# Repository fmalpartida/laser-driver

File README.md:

# Laser Driver
Small compact, constant current source for driving LEDs and lasers up to 4A with PWM capabilities and integrated support to drive 3 loads such as fans.

## Board specification
### Schematic
[Last version of the schematic](./documentation/laserDriver_schematic.pdf)

### Electrical characteristics
   **V(in) range:**  4V..18V, *observe input caps ratings*

   **Max. main load current:** 3.3A *observe inductor ratings*

   **Max. aux load currents:** 500mA *depends on transistor selection*

   **Dim. threshold voltage:** 1.2V

   **Duty cycle range:** 0%..100%

   **Soft start duration:** 1.2ms

   **Dim. frequency range:** 400Hz..4KHz

### Mechanical
   **Board dimensions:** 32mm x 32mm

   **Supply and main load dimming:** 1 x 3 pin, 2.54mm connector

   **Main load connector:** 1 x 2 pin, 2.54mm connector

   **Aux. load dimm. connector:** 1 x 3 pin, 2.54mm connector

   **Aux. load connector:** 3 x 2 pin, 2.54mm connector

   **PCB fabrication:** Pattern class 6, drills clase C. Any cheap PCB manufacturer should be more than capable of making your boards. *Do not shrink track widths.*

*Observe connector current ratings for your application.*

### Measured performance
   **Performance:** Measure performance 83% @ 12V, 1A load. Tested with a 3W LED.

## Operation and setup

Connect power supply to the supply and main load dimming connector observing the polarity
(V+, DIM, V-) within the board's tolerance and ensure that your supply is capable of sourcing
the current required by your load.

Connect the load (LED or laser driver) observing the polarity of your device.

If you use auxiliary loads connect them to the auxiliary load connectors and observe their polarity.
The board has built in freewheel diodes, you should be good to go with any type of load provided you don't
exceed switching ratings.

Each auxiliary load channel is controlled with a control signal from the aux load connector. By default
loads are inactive. A voltage level of 5V (depending on your FET selection) will activate each channel.

### Soft start
The board is configured to do a soft start. Apply a 1.2ms (minimum) pulse to the dimm pin before
starting the PWM operation.

## Waveforms and captures
A couple of waveform capture showing the performance of the driver. Measurement setup:
* Supply voltage: 5V
* Load current: 1A

To start the driver it needs a 1.1ms pulse on the dimming pin.

976Hz PWM duty cycle captures.

Raising edge, measuring directly the LED voltage on switch on. 10us, raising edge with very little
overshoot and ringing. Very decent current control and regulation.

Ripple and noise is around 20mV, I think that about half of it comes from my measurement setup. 20MHz
bandwidth limit.

## Disclaimer
The board has only been tested to switch a 3W LED driven at 1A. It should be more than capable of reaching
it's full specifications provided that you don't exceed the current ratings of the components you mount.

## License
The board is released under the CERN OHL v1.2 but if you like it and use it you can buy me some beer.
If you use it and/or do any derivative work from it, be nice and give attribution to the source.

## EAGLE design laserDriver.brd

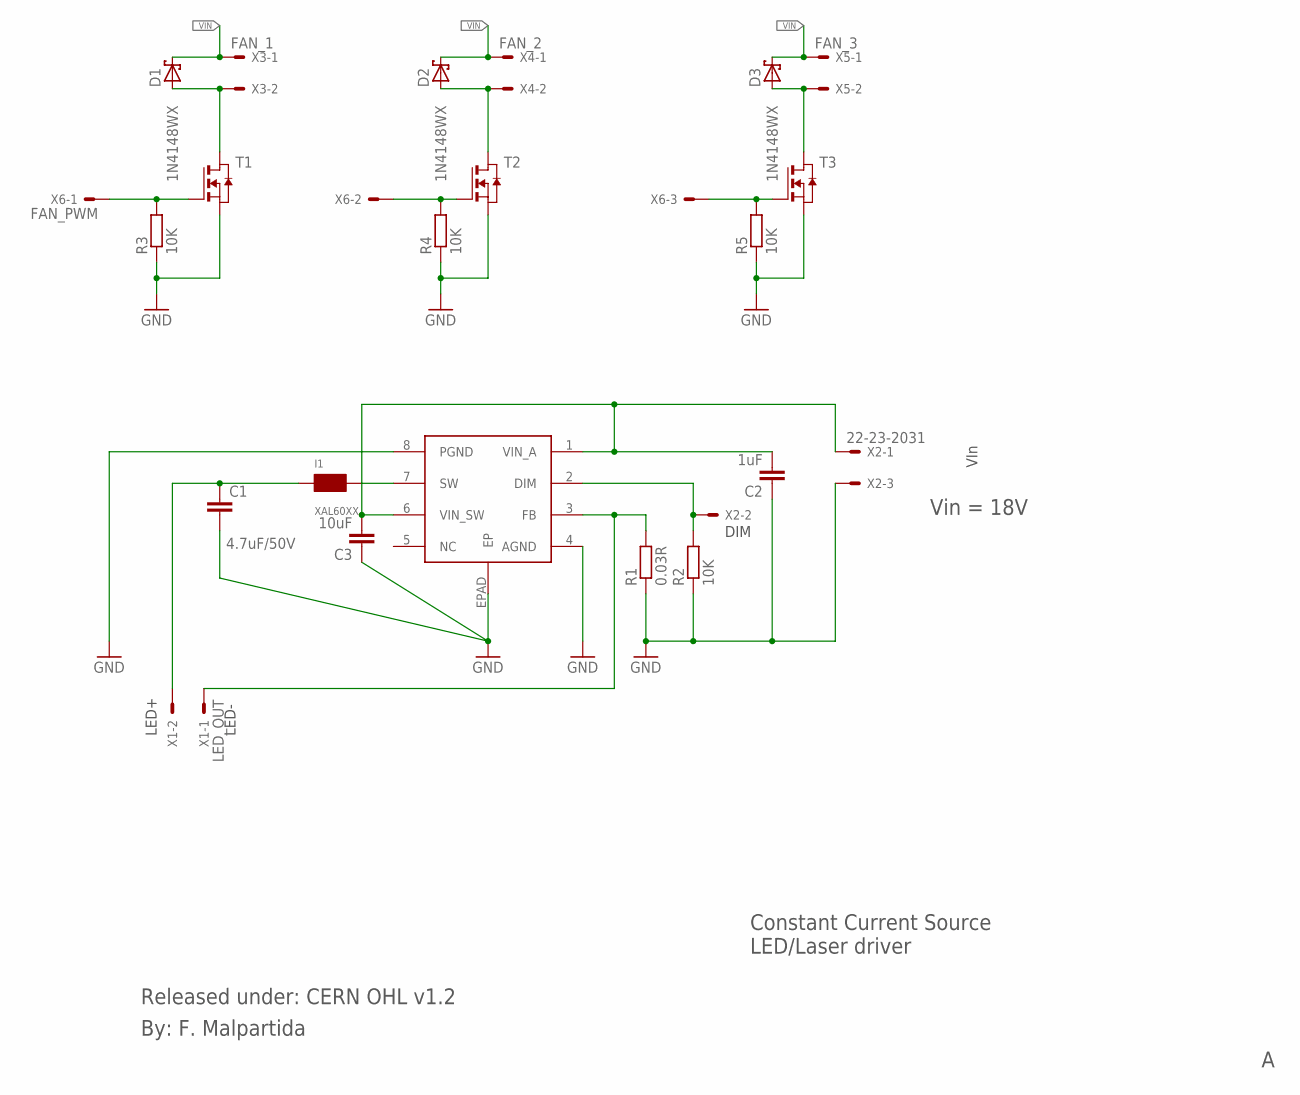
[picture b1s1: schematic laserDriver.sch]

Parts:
C1: 4.7uF/50V; C1206
C2: 1uF; C1206
C3: 10uF; C1206
D1, D2, D3: 1N4148WX; SOD323_ST
I1: XAL60XX
R1: 0.03R; R2512
R2, R3, R4, R5: 10K; M0805
T1, T2, T3: NMOSSOT23; SOT-23
U1: LED2001; SO08_PWR
X1: LED_OUT; 22-23-2021
X2: 22-23-2031
X3: FAN_1; 22-23-2021
X4: FAN_2; 22-23-2021
X5: FAN_3; 22-23-2021
X6: FAN_PWM; 22-23-2031

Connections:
GND: C1.2, C2.1, C3.1, R1.1, R2.1, R3.1, R4.1, R5.1, T1.2 (S), T2.2 (S), T3.2 (S), U1.4 (AGND), U1.8 (PGND), U1.EPAD (EP), X2.3
unnamed: R1.2, U1.3 (FB), X1.1
unnamed: I1.P$2, U1.7 (SW)
unnamed: D1.A, T1.1 (D), X3.2
unnamed: R2.2, U1.2 (DIM), X2.2
unnamed: D2.A, T2.1 (D), X4.2
unnamed: D3.A, T3.1 (D), X5.2
unnamed: R5.2, T3.3 (G), X6.3
unnamed: R4.2, T2.3 (G), X6.2
unnamed: R3.2, T1.3 (G), X6.1
_VIN: C2.2, C3.2, D1.C, D2.C, D3.C, U1.1 (VIN_A), U1.6 (VIN_SW), X2.1, X3.1, X4.1, X5.1
_VOUT: C1.1, I1.P$1, X1.2

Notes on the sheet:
LED+
LED-
VIn
DIM
Constant Current Source LED/Laser driver
Released under: CERN OHL v1.2
By: F. Malpartida
Vin = 18V

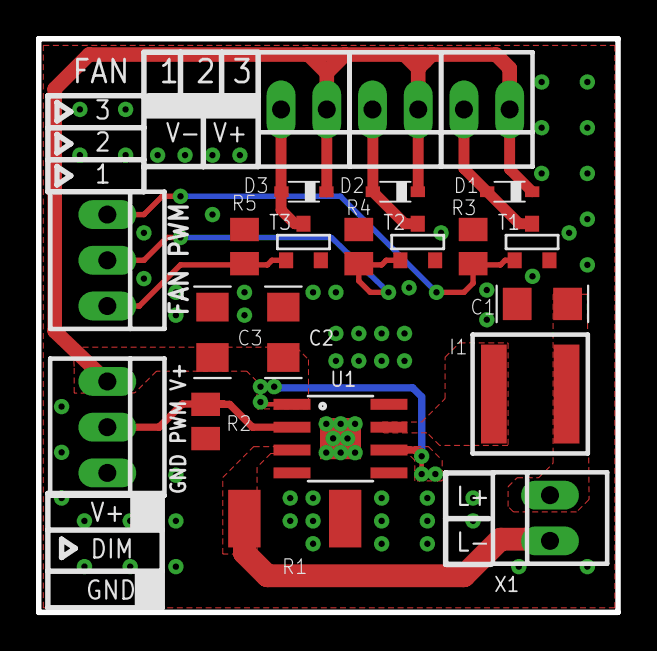
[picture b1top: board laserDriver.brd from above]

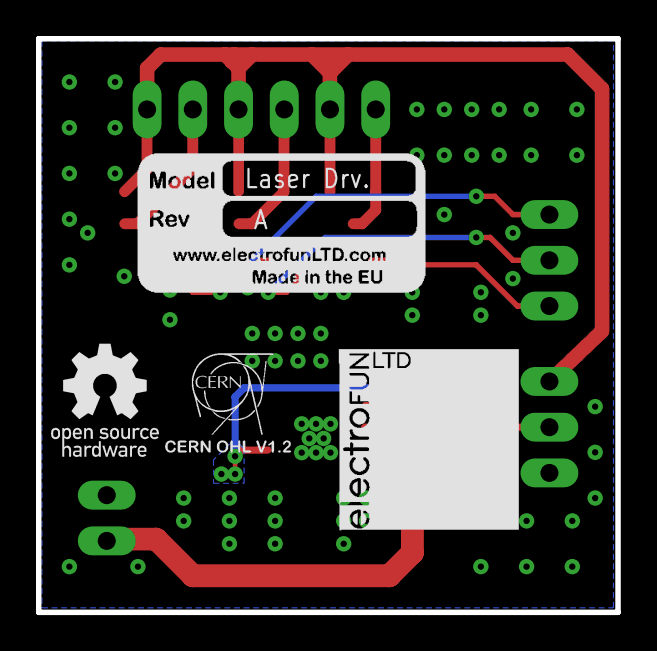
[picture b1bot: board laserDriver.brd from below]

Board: 2 copper layers, 32.2 x 31.9 mm, 26 parts (4 on the bottom side), 12 nets.

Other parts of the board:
U$1: OSHW
U$2: FMC_CERN_OHL
U$3: ELECTROFUN_10X10
U$4: BOARD_INFO_BMP_SMALL

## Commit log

2016-05-18 First README version
2016-05-18 Added licensing terms
2016-05-18 Laser driver board and schematic. Revision A.
2016-05-18 Added pdf schematic.
2016-05-18 Added images for documentation.
2016-05-18 Small update on read me file.
2016-05-18 Changed image formatting.
2016-05-18 Minor PCB touch ups. Updated README file.
2016-05-18 Arranging images.
2016-05-18 Adjusted images.
2016-05-18 README formating.
2016-05-18 Wrap up README for release.
2016-05-18 Added schematic image.
2016-05-18 Waveform measurements added to the read me file.
2016-05-18 Updated ripple image.
2016-05-21 Minor changes.
2017-03-26 Test SW added.
